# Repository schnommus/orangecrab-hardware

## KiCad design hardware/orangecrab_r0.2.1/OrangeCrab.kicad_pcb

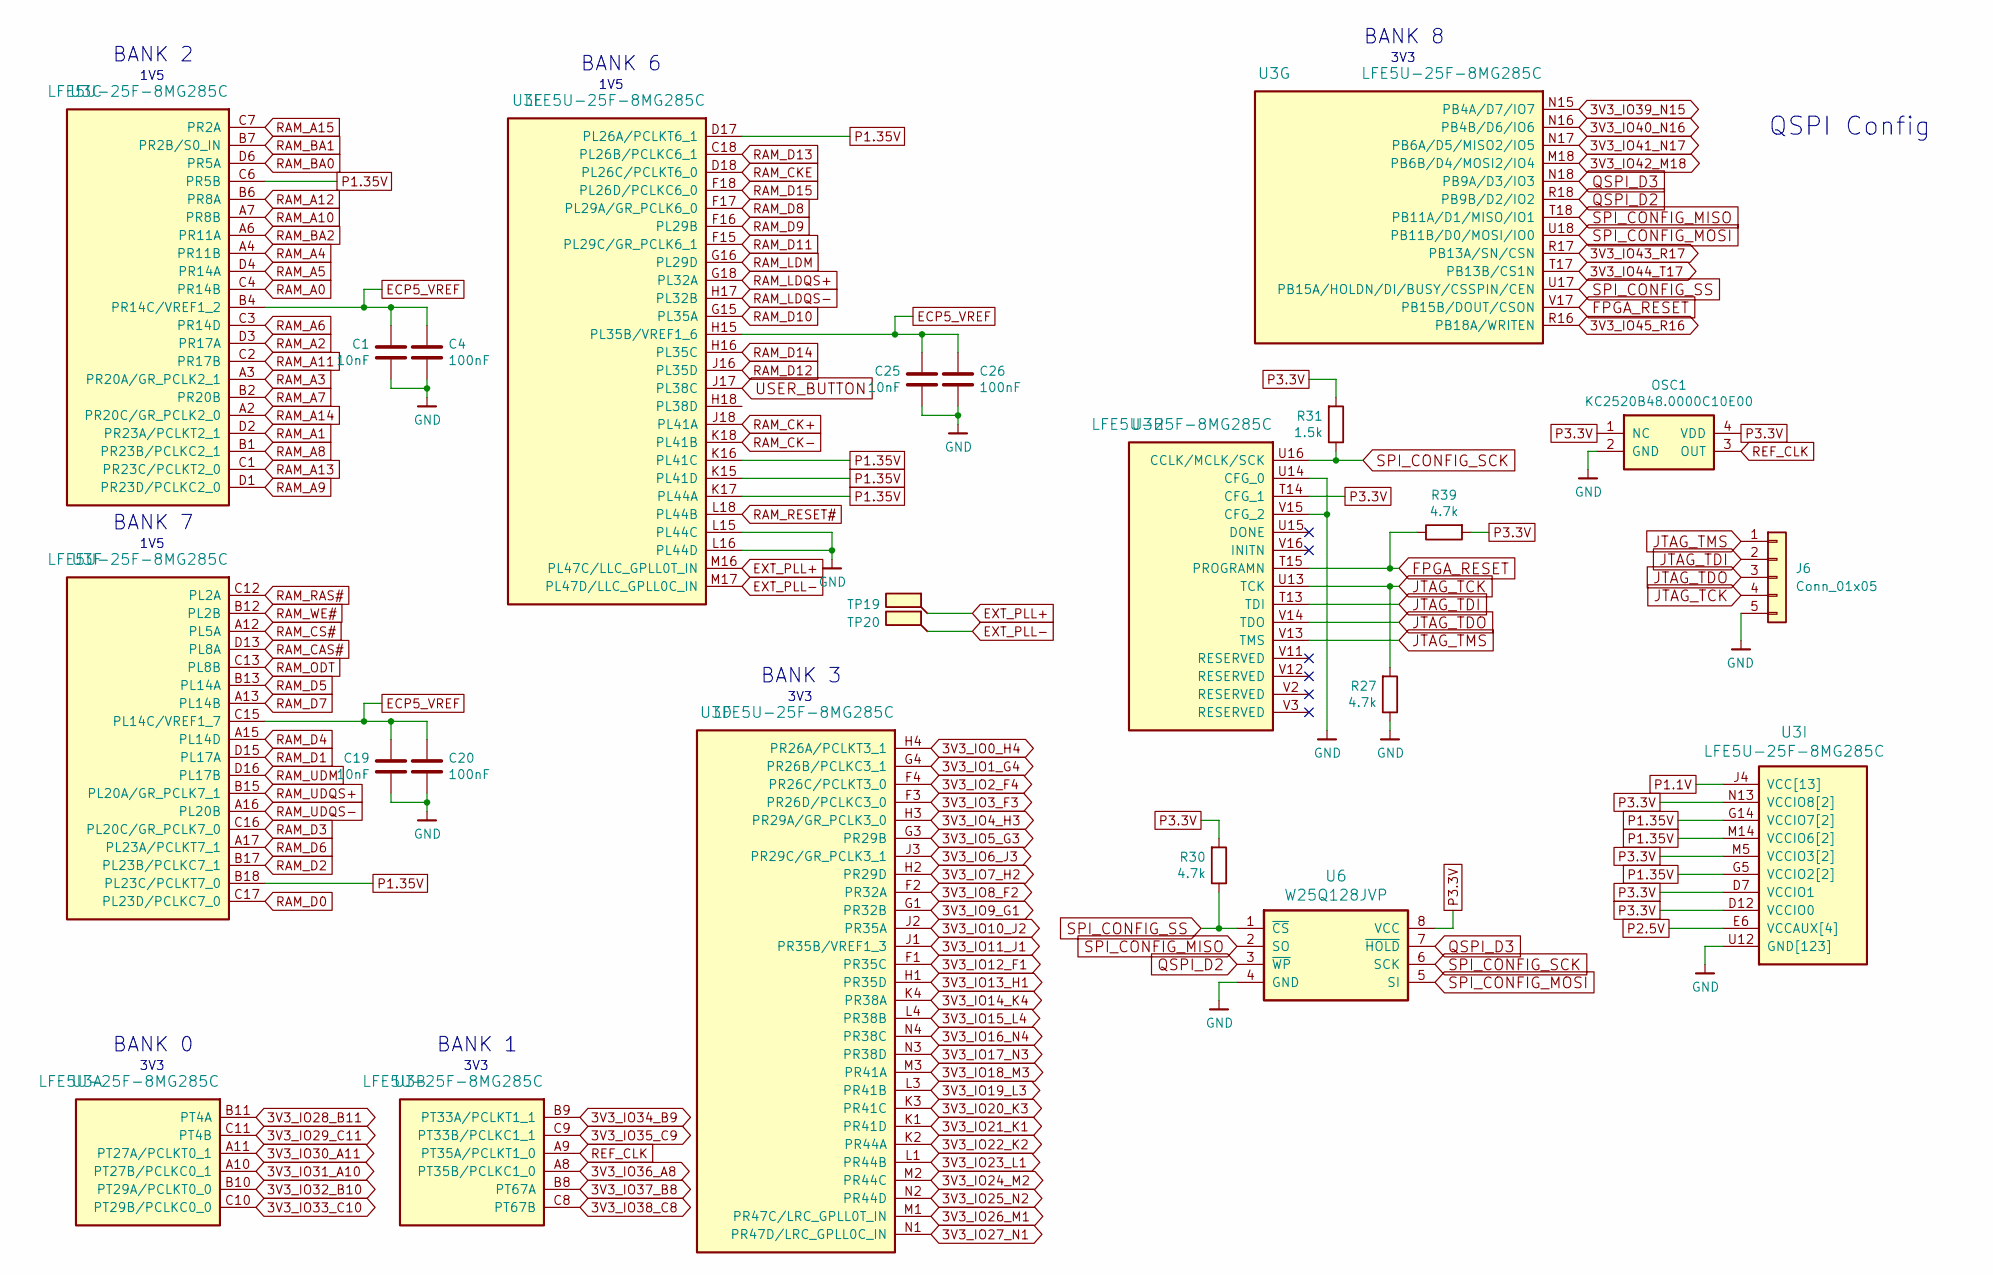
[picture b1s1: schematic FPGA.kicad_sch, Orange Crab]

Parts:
C1, C19, C25: 10nF; C_0201_0603Metric; lcsc# C272853
C4, C20, C26: 100nF; C_0201_0603Metric; lcsc# C467016
J6: Conn_01x05; PinHeader_1x05_P2.54mm_Vertical
OSC1: KC2520B48.0000C10E00; Oscilator_2.5x2.0; lcsc# C669070
R27, R30, R39: 4.7k; R_0201_0603Metric
R31: 1.5k; R_0201_0603Metric
TP19, TP20: SMD_TP; TestPoint_Pad_D0.5mm
U3: LFE5U-25F-8MG285C; csBGA285
U6: W25Q128JVP; WSON-8-1EP_6x5mm_P1.27mm_EP3.4x4mm; lcsc# C190862

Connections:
3V3_IO0_H4: U3.H4 (PR26A/PCLKT3_1); also elsewhere on the board
3V3_IO1_G4: U3.G4 (PR26B/PCLKC3_1); also elsewhere on the board
3V3_IO2_F4: U3.F4 (PR26C/PCLKT3_0); also elsewhere on the board
3V3_IO3_F3: U3.F3 (PR26D/PCLKC3_0); also elsewhere on the board
3V3_IO4_H3: U3.H3 (PR29A/GR_PCLK3_0); also elsewhere on the board
3V3_IO5_G3: U3.G3 (PR29B); also elsewhere on the board
3V3_IO6_J3: U3.J3 (PR29C/GR_PCLK3_1); also elsewhere on the board
3V3_IO7_H2: U3.H2 (PR29D); also elsewhere on the board
3V3_IO8_F2: U3.F2 (PR32A); also elsewhere on the board
3V3_IO9_G1: U3.G1 (PR32B); also elsewhere on the board
3V3_IO10_J2: U3.J2 (PR35A); also elsewhere on the board
3V3_IO11_J1: U3.J1 (PR35B/VREF1_3); also elsewhere on the board
3V3_IO12_F1: U3.F1 (PR35C); also elsewhere on the board
3V3_IO13_H1: U3.H1 (PR35D); also elsewhere on the board
3V3_IO14_K4: U3.K4 (PR38A); also elsewhere on the board
3V3_IO15_L4: U3.L4 (PR38B); also elsewhere on the board
3V3_IO16_N4: U3.N4 (PR38C); also elsewhere on the board
3V3_IO17_N3: U3.N3 (PR38D); also elsewhere on the board
3V3_IO18_M3: U3.M3 (PR41A); also elsewhere on the board
3V3_IO19_L3: U3.L3 (PR41B); also elsewhere on the board
3V3_IO20_K3: U3.K3 (PR41C); also elsewhere on the board
3V3_IO21_K1: U3.K1 (PR41D); also elsewhere on the board
3V3_IO22_K2: U3.K2 (PR44A); also elsewhere on the board
3V3_IO23_L1: U3.L1 (PR44B); also elsewhere on the board
3V3_IO24_M2: U3.M2 (PR44C); also elsewhere on the board
3V3_IO25_N2: U3.N2 (PR44D); also elsewhere on the board
3V3_IO26_M1: U3.M1 (PR47C/LRC_GPLL0T_IN); also elsewhere on the board
3V3_IO27_N1: U3.N1 (PR47D/LRC_GPLL0C_IN); also elsewhere on the board
3V3_IO28_B11: U3.B11 (PT4A); also elsewhere on the board
3V3_IO29_C11: U3.C11 (PT4B); also elsewhere on the board
3V3_IO30_A11: U3.A11 (PT27A/PCLKT0_1); also elsewhere on the board
3V3_IO31_A10: U3.A10 (PT27B/PCLKC0_1); also elsewhere on the board
3V3_IO32_B10: U3.B10 (PT29A/PCLKT0_0); also elsewhere on the board
3V3_IO33_C10: U3.C10 (PT29B/PCLKC0_0); also elsewhere on the board
3V3_IO34_B9: U3.B9 (PT33A/PCLKT1_1); also elsewhere on the board
3V3_IO35_C9: U3.C9 (PT33B/PCLKC1_1); also elsewhere on the board
3V3_IO36_A8: U3.A8 (PT35B/PCLKC1_0); also elsewhere on the board
3V3_IO37_B8: U3.B8 (PT67A); also elsewhere on the board
3V3_IO38_C8: U3.C8 (PT67B); also elsewhere on the board
3V3_IO39_N15: U3.N15 (PB4A/D7/IO7); also elsewhere on the board
3V3_IO40_N16: U3.N16 (PB4B/D6/IO6); also elsewhere on the board
3V3_IO41_N17: U3.N17 (PB6A/D5/MISO2/IO5); also elsewhere on the board
3V3_IO42_M18: U3.M18 (PB6B/D4/MOSI2/IO4); also elsewhere on the board
3V3_IO43_R17: U3.R17 (PB13A/SN/CSN); also elsewhere on the board
3V3_IO44_T17: U3.T17 (PB13B/CS1N); also elsewhere on the board
3V3_IO45_R16: U3.R16 (PB18A/WRITEN); also elsewhere on the board
ECP5_VREF: C1.1, C4.1, C19.1, C20.1, C25.1, C26.1, U3.B4 (PR14C/VREF1_2), U3.C15 (PL14C/VREF1_7), U3.H15 (PL35B/VREF1_6); also elsewhere on the board
EXT_PLL+: TP19.1, U3.M16 (PL47C/LLC_GPLL0T_IN)
EXT_PLL-: TP20.1, U3.M17 (PL47D/LLC_GPLL0C_IN)
FPGA_RESET: R39.1, U3.T15 (PROGRAMN), U3.V17 (PB15B/DOUT/CSON)
GND: C1.2, C4.2, C19.2, C20.2, C25.2, C26.2, J6.5, OSC1.2 (GND), R27.1, U3.B3 (GND[123]), U3.B16 (GND[123]), U3.E5 (GND[123]), U3.E7 (GND[123]), U3.E8 (GND[123]), U3.E9 (GND[123]), U3.E10 (GND[123]), U3.E11 (GND[123]), U3.E12 (GND[123]), U3.E14 (GND[123]), U3.F5 (GND[123]), U3.F6 (GND[123]), U3.F7 (GND[123]), U3.F8 (GND[123]), U3.F9 (GND[123]), U3.F10 (GND[123]), U3.F11 (GND[123]), U3.F12 (GND[123]), U3.F13 (GND[123]), U3.F14 (GND[123]), U3.G2 (GND[123]), U3.G6 (GND[123]), U3.G7 (GND[123]), U3.G8 (GND[123]), U3.G9 (GND[123]), U3.G10 (GND[123]), U3.G11 (GND[123]), U3.G12 (GND[123]), U3.G13 (GND[123]), U3.G17 (GND[123]), U3.H6 (GND[123]), U3.H7 (GND[123]), U3.H8 (GND[123]), U3.H9 (GND[123]), U3.H10 (GND[123]), U3.H11 (GND[123]), U3.H12 (GND[123]), U3.H13 (GND[123]), U3.J6 (GND[123]), U3.J7 (GND[123]), U3.J8 (GND[123]), U3.J9 (GND[123]), U3.J10 (GND[123]), U3.J11 (GND[123]), U3.J12 (GND[123]), U3.J13 (GND[123]), U3.K5 (GND[123]), U3.K6 (GND[123]), U3.K7 (GND[123]), U3.K8 (GND[123]), U3.K9 (GND[123]), U3.K10 (GND[123]), U3.K11 (GND[123]), U3.K12 (GND[123]), U3.K13 (GND[123]), U3.K14 (GND[123]), U3.L2 (GND[123]), U3.L5 (GND[123]), U3.L6 (GND[123]), U3.L7 (GND[123]), U3.L8 (GND[123]), U3.L9 (GND[123]), U3.L10 (GND[123]), U3.L11 (GND[123]), U3.L12 (GND[123]), U3.L13 (GND[123]), U3.L14 (GND[123]), U3.L15 (PL44C), U3.L16 (PL44D), U3.L17 (GND[123]), U3.M6 (GND[123]), U3.M7 (GND[123]), U3.M8 (GND[123]), U3.M9 (GND[123]), U3.M10 (GND[123]), U3.M11 (GND[123]), U3.M12 (GND[123]), U3.M13 (GND[123]), U3.N7 (GND[123]), U3.N8 (GND[123]), U3.N9 (GND[123]), U3.N10 (GND[123]), U3.N11 (GND[123]), U3.N12 (GND[123]), U3.P5 (GND[123]), U3.P6 (GND[123]), U3.P8 (GND[123]), U3.P10 (GND[123]), U3.P12 (GND[123]), U3.R1 (GND[123]), U3.R2 (GND[123]), U3.R3 (GND[123]), U3.R10 (GND[123]), U3.T1 (GND[123]), U3.T2 (GND[123]), U3.T3 (GND[123]), U3.T4 (GND[123]), U3.T5 (GND[123]), U3.T6 (GND[123]), U3.T7 (GND[123]), U3.T8 (GND[123]), U3.T9 (GND[123]), U3.T10 (GND[123]), U3.T11 (GND[123]), U3.T12 (GND[123]), U3.T16 (GND[123]), U3.U1 (GND[123]), U3.U2 (GND[123]), U3.U3 (GND[123]), U3.U4 (GND[123]), U3.U5 (GND[123]), U3.U6 (GND[123]), U3.U7 (GND[123]), U3.U8 (GND[123]), U3.U9 (GND[123]), U3.U10 (GND[123]), U3.U11 (GND[123]), U3.U12 (GND[123]), U3.U14 (CFG_0), U3.V4 (GND[123]), U3.V5 (GND[123]), U3.V6 (GND[123]), U3.V7 (GND[123]), U3.V8 (GND[123]), U3.V9 (GND[123]), U3.V10 (GND[123]), U3.V15 (CFG_2), U6.4 (GND); also elsewhere on the board
JTAG_TCK: J6.4, R27.2, U3.U13 (TCK); also elsewhere on the board
JTAG_TDI: J6.2, U3.T13 (TDI); also elsewhere on the board
JTAG_TDO: J6.3, U3.V14 (TDO); also elsewhere on the board
JTAG_TMS: J6.1, U3.V13 (TMS); also elsewhere on the board
P1.1V: U3.D8 (VCC[13]), U3.D9 (VCC[13]), U3.D10 (VCC[13]), U3.D11 (VCC[13]), U3.J4 (VCC[13]), U3.J5 (VCC[13]), U3.J14 (VCC[13]), U3.J15 (VCC[13]), U3.M4 (VCC[13]), U3.M15 (VCC[13]), U3.P7 (VCC[13]), U3.P9 (VCC[13]), U3.P11 (VCC[13]); also elsewhere on the board
P1.35V: U3.B18 (PL23C/PCLKT7_0), U3.C6 (PR5B), U3.D17 (PL26A/PCLKT6_1), U3.G5 (VCCIO2[2]), U3.G14 (VCCIO7[2]), U3.H5 (VCCIO2[2]), U3.H14 (VCCIO7[2]), U3.K15 (PL41D), U3.K16 (PL41C), U3.K17 (PL44A), U3.M14 (VCCIO6[2]), U3.N14 (VCCIO6[2]); also elsewhere on the board
P2.5V: U3.E6 (VCCAUX[4]), U3.E13 (VCCAUX[4]), U3.N6 (VCCAUX[4]), U3.P13 (VCCAUX[4]); also elsewhere on the board
P3.3V: OSC1.1 (NC), OSC1.4 (VDD), R30.2, R31.2, R39.2, U3.D7 (VCCIO1), U3.D12 (VCCIO0), U3.M5 (VCCIO3[2]), U3.N5 (VCCIO3[2]), U3.N13 (VCCIO8[2]), U3.P14 (VCCIO8[2]), U3.T14 (CFG_1), U6.8 (VCC); also elsewhere on the board
QSPI_D2: U3.R18 (PB9B/D2/IO2), U6.3 (~WP)
QSPI_D3: U3.N18 (PB9A/D3/IO3), U6.7 (~HOLD)
RAM_A0: U3.C4 (PR14B); also elsewhere on the board
RAM_A1: U3.D2 (PR23A/PCLKT2_1); also elsewhere on the board
RAM_A2: U3.D3 (PR17A); also elsewhere on the board
RAM_A3: U3.A3 (PR20A/GR_PCLK2_1); also elsewhere on the board
RAM_A4: U3.A4 (PR11B); also elsewhere on the board
RAM_A5: U3.D4 (PR14A); also elsewhere on the board
RAM_A6: U3.C3 (PR14D); also elsewhere on the board
RAM_A7: U3.B2 (PR20B); also elsewhere on the board
RAM_A8: U3.B1 (PR23B/PCLKC2_1); also elsewhere on the board
RAM_A9: U3.D1 (PR23D/PCLKC2_0); also elsewhere on the board
RAM_A10: U3.A7 (PR8B); also elsewhere on the board
RAM_A11: U3.C2 (PR17B); also elsewhere on the board
RAM_A12: U3.B6 (PR8A); also elsewhere on the board
RAM_A13: U3.C1 (PR23C/PCLKT2_0); also elsewhere on the board
RAM_A14: U3.A2 (PR20C/GR_PCLK2_0); also elsewhere on the board
RAM_A15: U3.C7 (PR2A); also elsewhere on the board
RAM_BA0: U3.D6 (PR5A); also elsewhere on the board
RAM_BA1: U3.B7 (PR2B/S0_IN); also elsewhere on the board
RAM_BA2: U3.A6 (PR11A); also elsewhere on the board
RAM_CAS#: U3.D13 (PL8A); also elsewhere on the board
RAM_CK+: U3.J18 (PL41A); also elsewhere on the board
RAM_CK-: U3.K18 (PL41B); also elsewhere on the board
RAM_CKE: U3.D18 (PL26C/PCLKT6_0); also elsewhere on the board
RAM_CS#: U3.A12 (PL5A); also elsewhere on the board
RAM_D0: U3.C17 (PL23D/PCLKC7_0); also elsewhere on the board
RAM_D1: U3.D15 (PL17A); also elsewhere on the board
RAM_D2: U3.B17 (PL23B/PCLKC7_1); also elsewhere on the board
RAM_D3: U3.C16 (PL20C/GR_PCLK7_0); also elsewhere on the board
RAM_D4: U3.A15 (PL14D); also elsewhere on the board
RAM_D5: U3.B13 (PL14A); also elsewhere on the board
RAM_D6: U3.A17 (PL23A/PCLKT7_1); also elsewhere on the board
RAM_D7: U3.A13 (PL14B); also elsewhere on the board
RAM_D8: U3.F17 (PL29A/GR_PCLK6_0); also elsewhere on the board
RAM_D9: U3.F16 (PL29B); also elsewhere on the board
RAM_D10: U3.G15 (PL35A); also elsewhere on the board
RAM_D11: U3.F15 (PL29C/GR_PCLK6_1); also elsewhere on the board
RAM_D12: U3.J16 (PL35D); also elsewhere on the board
RAM_D13: U3.C18 (PL26B/PCLKC6_1); also elsewhere on the board
RAM_D14: U3.H16 (PL35C); also elsewhere on the board
RAM_D15: U3.F18 (PL26D/PCLKC6_0); also elsewhere on the board
RAM_LDM: U3.G16 (PL29D); also elsewhere on the board
RAM_LDQS+: U3.G18 (PL32A); also elsewhere on the board
RAM_LDQS-: U3.H17 (PL32B); also elsewhere on the board
RAM_ODT: U3.C13 (PL8B); also elsewhere on the board
RAM_RAS#: U3.C12 (PL2A); also elsewhere on the board
RAM_RESET#: U3.L18 (PL44B); also elsewhere on the board
RAM_UDM: U3.D16 (PL17B); also elsewhere on the board
RAM_UDQS+: U3.B15 (PL20A/GR_PCLK7_1); also elsewhere on the board
RAM_UDQS-: U3.A16 (PL20B); also elsewhere on the board
RAM_WE#: U3.B12 (PL2B); also elsewhere on the board
REF_CLK: OSC1.3 (OUT), U3.A9 (PT35A/PCLKT1_0)
SPI_CONFIG_MISO: U3.T18 (PB11A/D1/MISO/IO1), U6.2 (SO)
SPI_CONFIG_MOSI: U3.U18 (PB11B/D0/MOSI/IO0), U6.5 (SI)
SPI_CONFIG_SCK: R31.1, U3.U16 (CCLK/MCLK/SCK), U6.6 (SCK)
SPI_CONFIG_SS: R30.1, U3.U17 (PB15A/HOLDN/DI/BUSY/CSSPIN/CEN), U6.1 (~CS)
USER_BUTTON: U3.J17 (PL38C)

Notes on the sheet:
BANK 0
3V3
BANK 8
1V5
BANK 6
BANK 1
3V3
1V5
QSPI Config
BANK 7
BANK 2
BANK 3

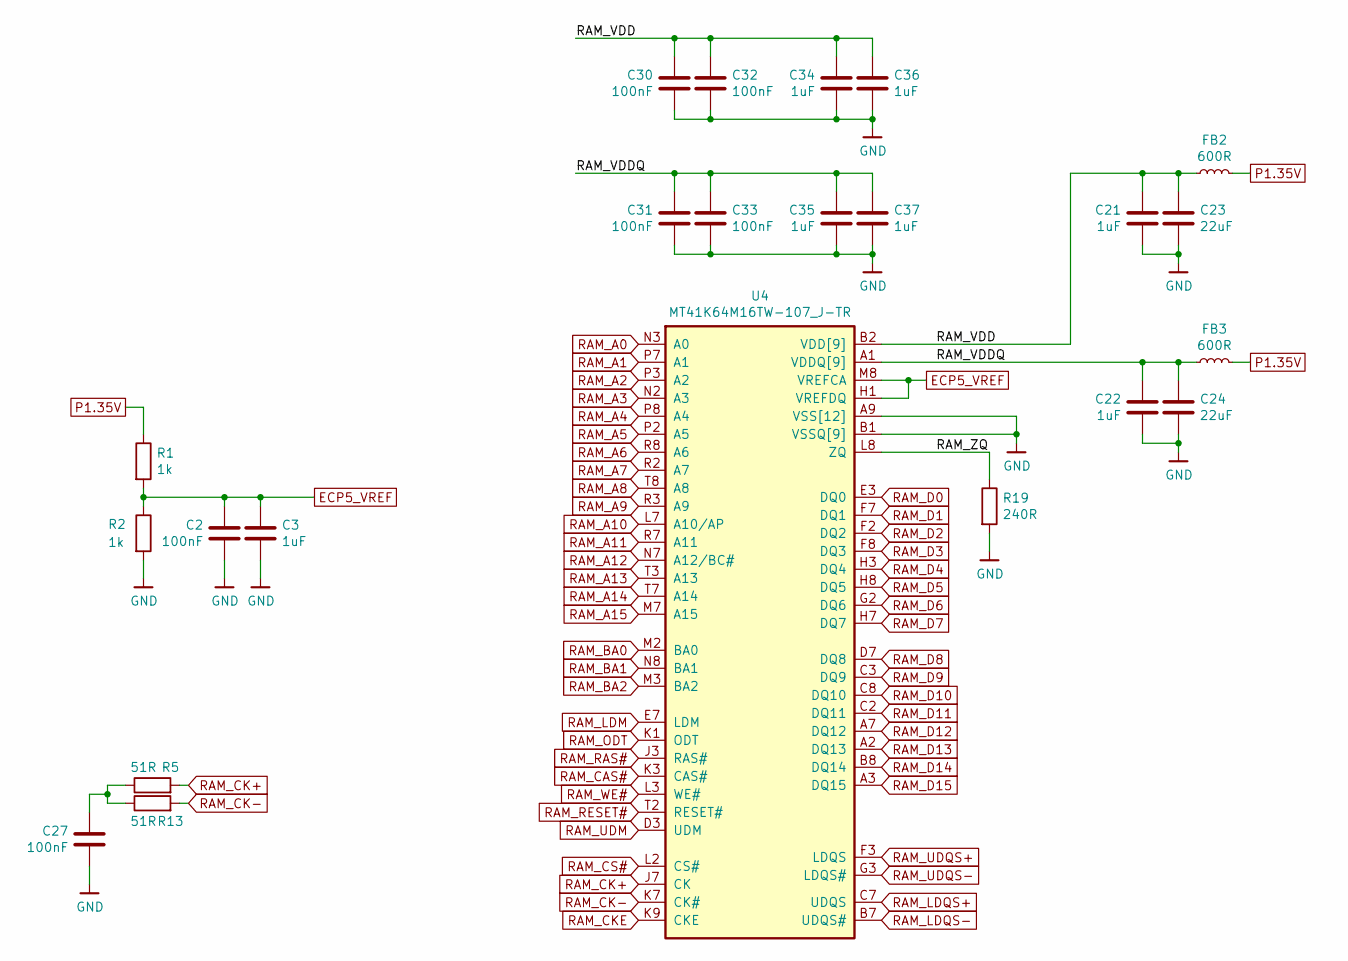
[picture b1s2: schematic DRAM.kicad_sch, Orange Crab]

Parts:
C2, C27, C30, C31, C32, C33: 100nF; C_0201_0603Metric; lcsc# C467016
C3, C21, C22, C34, C35, C36, C37: 1uF; C_0402_1005Metric; lcsc# C325464
C23, C24: 22uF; C_0603_1608Metric; lcsc# C109448
FB2, FB3: 600R; L_0402_1005Metric; lcsc# C87550
R1, R2: 1k; R_0201_0603Metric
R5, R13: 51R; R_0201_0603Metric
R19: 240R; R_0402_1005Metric
U4: MT41K64M16TW-107_J-TR; BGA-96_9.0x13.0mm_Layout2x3x16_P0.8mm; lcsc# C75475

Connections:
/DRAM/RAM_VDD: C21.1, C23.1, C30.1, C32.1, C34.1, C36.1, FB2.1, U4.B2 (VDD[9]), U4.D9 (VDD), U4.G7 (VDD), U4.K2 (VDD), U4.K8 (VDD), U4.N1 (VDD), U4.N9 (VDD), U4.R1 (VDD), U4.R9 (VDD)
/DRAM/RAM_VDDQ: C22.1, C24.1, C31.1, C33.1, C35.1, C37.1, FB3.1, U4.A1 (VDDQ[9]), U4.A8 (VDDQ), U4.C1 (VDDQ), U4.C9 (VDDQ), U4.D2 (VDDQ), U4.E9 (VDDQ), U4.F1 (VDDQ), U4.H2 (VDDQ), U4.H9 (VDDQ)
/DRAM/RAM_ZQ: R19.1, U4.L8 (ZQ)
ECP5_VREF: C2.1, C3.1, R1.2, R2.1, U4.H1 (VREFDQ), U4.M8 (VREFCA); also elsewhere on the board
GND: C2.2, C3.2, C21.2, C22.2, C23.2, C24.2, C27.2, C30.2, C31.2, C32.2, C33.2, C34.2, C35.2, C36.2, C37.2, R2.2, R19.2, U4.A9 (VSS[12]), U4.B1 (VSSQ[9]), U4.B3 (VSS), U4.B9 (VSSQ), U4.D1 (VSSQ), U4.D8 (VSSQ), U4.E1 (VSS), U4.E2 (VSSQ), U4.E8 (VSSQ), U4.F9 (VSSQ), U4.G1 (VSSQ), U4.G9 (VSSQ), U4.J2 (VSS), U4.J8 (VSS), U4.M1 (VSS), U4.M9 (VSS), U4.P1 (VSS), U4.P9 (VSS), U4.T1 (VSS), U4.T9 (VSS); also elsewhere on the board
unnamed: C27.1, R5.1, R13.1
P1.35V: FB2.2, FB3.2, R1.1; also elsewhere on the board
RAM_A0: U4.N3 (A0); also elsewhere on the board
RAM_A1: U4.P7 (A1); also elsewhere on the board
RAM_A2: U4.P3 (A2); also elsewhere on the board
RAM_A3: U4.N2 (A3); also elsewhere on the board
RAM_A4: U4.P8 (A4); also elsewhere on the board
RAM_A5: U4.P2 (A5); also elsewhere on the board
RAM_A6: U4.R8 (A6); also elsewhere on the board
RAM_A7: U4.R2 (A7); also elsewhere on the board
RAM_A8: U4.T8 (A8); also elsewhere on the board
RAM_A9: U4.R3 (A9); also elsewhere on the board
RAM_A10: U4.L7 (A10/AP); also elsewhere on the board
RAM_A11: U4.R7 (A11); also elsewhere on the board
RAM_A12: U4.N7 (A12/BC#); also elsewhere on the board
RAM_A13: U4.T3 (A13); also elsewhere on the board
RAM_A14: U4.T7 (A14); also elsewhere on the board
RAM_A15: U4.M7 (A15); also elsewhere on the board
RAM_BA0: U4.M2 (BA0); also elsewhere on the board
RAM_BA1: U4.N8 (BA1); also elsewhere on the board
RAM_BA2: U4.M3 (BA2); also elsewhere on the board
RAM_CAS#: U4.K3 (CAS#); also elsewhere on the board
RAM_CK+: R5.2, U4.J7 (CK); also elsewhere on the board
RAM_CK-: R13.2, U4.K7 (CK#); also elsewhere on the board
RAM_CKE: U4.K9 (CKE); also elsewhere on the board
RAM_CS#: U4.L2 (CS#); also elsewhere on the board
RAM_D0: U4.E3 (DQ0); also elsewhere on the board
RAM_D1: U4.F7 (DQ1); also elsewhere on the board
RAM_D2: U4.F2 (DQ2); also elsewhere on the board
RAM_D3: U4.F8 (DQ3); also elsewhere on the board
RAM_D4: U4.H3 (DQ4); also elsewhere on the board
RAM_D5: U4.H8 (DQ5); also elsewhere on the board
RAM_D6: U4.G2 (DQ6); also elsewhere on the board
RAM_D7: U4.H7 (DQ7); also elsewhere on the board
RAM_D8: U4.D7 (DQ8); also elsewhere on the board
RAM_D9: U4.C3 (DQ9); also elsewhere on the board
RAM_D10: U4.C8 (DQ10); also elsewhere on the board
RAM_D11: U4.C2 (DQ11); also elsewhere on the board
RAM_D12: U4.A7 (DQ12); also elsewhere on the board
RAM_D13: U4.A2 (DQ13); also elsewhere on the board
RAM_D14: U4.B8 (DQ14); also elsewhere on the board
RAM_D15: U4.A3 (DQ15); also elsewhere on the board
RAM_LDM: U4.E7 (LDM); also elsewhere on the board
RAM_LDQS+: U4.C7 (UDQS); also elsewhere on the board
RAM_LDQS-: U4.B7 (UDQS#); also elsewhere on the board
RAM_ODT: U4.K1 (ODT); also elsewhere on the board
RAM_RAS#: U4.J3 (RAS#); also elsewhere on the board
RAM_RESET#: U4.T2 (RESET#); also elsewhere on the board
RAM_UDM: U4.D3 (UDM); also elsewhere on the board
RAM_UDQS+: U4.F3 (LDQS); also elsewhere on the board
RAM_UDQS-: U4.G3 (LDQS#); also elsewhere on the board
RAM_WE#: U4.L3 (WE#); also elsewhere on the board

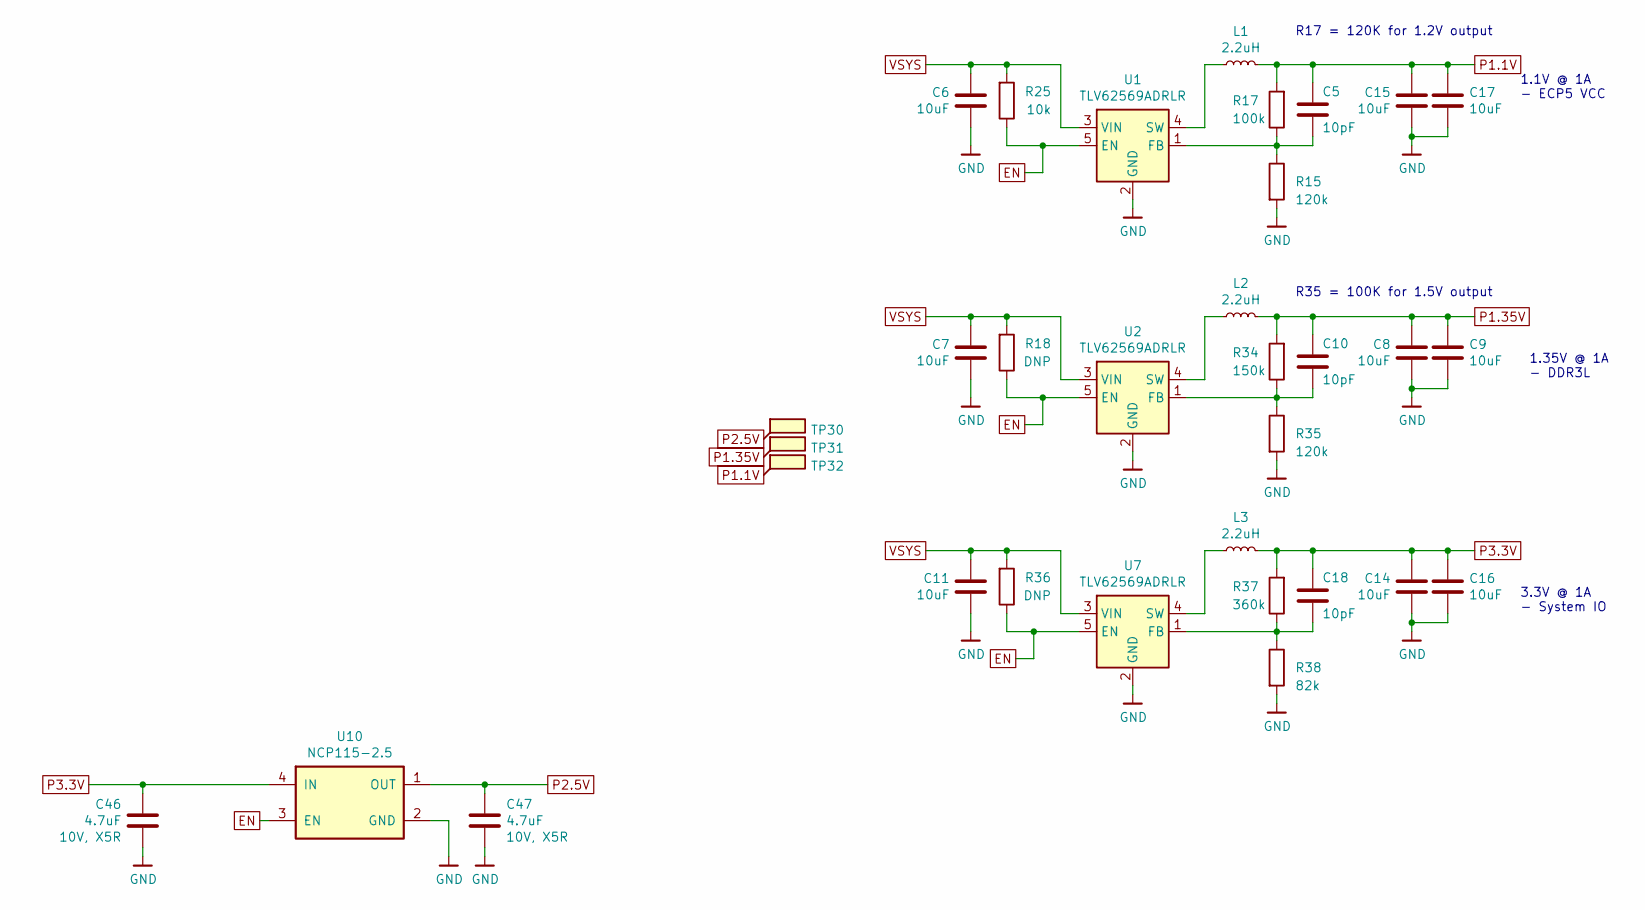
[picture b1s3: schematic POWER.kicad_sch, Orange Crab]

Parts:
C5, C10, C18: 10pF; C_0201_0603Metric; lcsc# C526922
C6, C7, C8, C9, C11, C14, C15, C16, C17: 10uF; C_0402_1005Metric; lcsc# C105884
C46, C47: 4.7uF; C_0402_1005Metric; lcsc# C326586
L1, L2, L3: 2.2uH; L_0805_2012Metric; lcsc# C216156
R15, R35: 120k; R_0201_0603Metric
R17: 100k; R_0201_0603Metric
R18, R36: DNP; R_0201_0603Metric
R25: 10k; R_0201_0603Metric
R34: 150k; R_0201_0603Metric
R37: 360k; R_0201_0603Metric
R38: 82k; R_0201_0603Metric
TP30, TP31, TP32: SMD_TP; TestPoint_Pad_D0.5mm
U1, U2, U7: TLV62569ADRLR; SOT-563; lcsc# C398367
U10: NCP115-2.5; Texas_X2SON-4_1x1mm_P0.65mm

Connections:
EN: R18.1, R25.1, R36.1, U1.5 (EN), U2.5 (EN), U7.5 (EN), U10.3 (EN)
GND: C6.1, C7.1, C8.1, C9.1, C11.1, C14.1, C15.1, C16.1, C17.1, C46.2, C47.2, R15.2, R35.2, R38.2, U1.2 (GND), U2.2 (GND), U7.2 (GND), U10.2 (GND); also elsewhere on the board
unnamed: C5.1, R15.1, R17.1, U1.1 (FB)
unnamed: L1.1, U1.4 (SW)
unnamed: C10.1, R34.1, R35.1, U2.1 (FB)
unnamed: L2.1, U2.4 (SW)
unnamed: C18.1, R37.1, R38.1, U7.1 (FB)
unnamed: L3.1, U7.4 (SW)
P1.1V: C5.2, C15.2, C17.2, L1.2, R17.2, TP32.1; also elsewhere on the board
P1.35V: C8.2, C9.2, C10.2, L2.2, R34.2, TP31.1; also elsewhere on the board
P2.5V: C47.1, TP30.1, U10.1 (OUT); also elsewhere on the board
P3.3V: C14.2, C16.2, C18.2, C46.1, L3.2, R37.2, U10.4 (IN); also elsewhere on the board
VSYS: C6.2, C7.2, C11.2, R18.2, R25.2, R36.2, U1.3 (VIN), U2.3 (VIN), U7.3 (VIN); also elsewhere on the board

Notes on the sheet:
1.35V @ 1A - DDR3L
3.3V @ 1A - System IO
R35 = 100K for 1.5V output
R17 = 120K for 1.2V output
1.1V @ 1A - ECP5 VCC

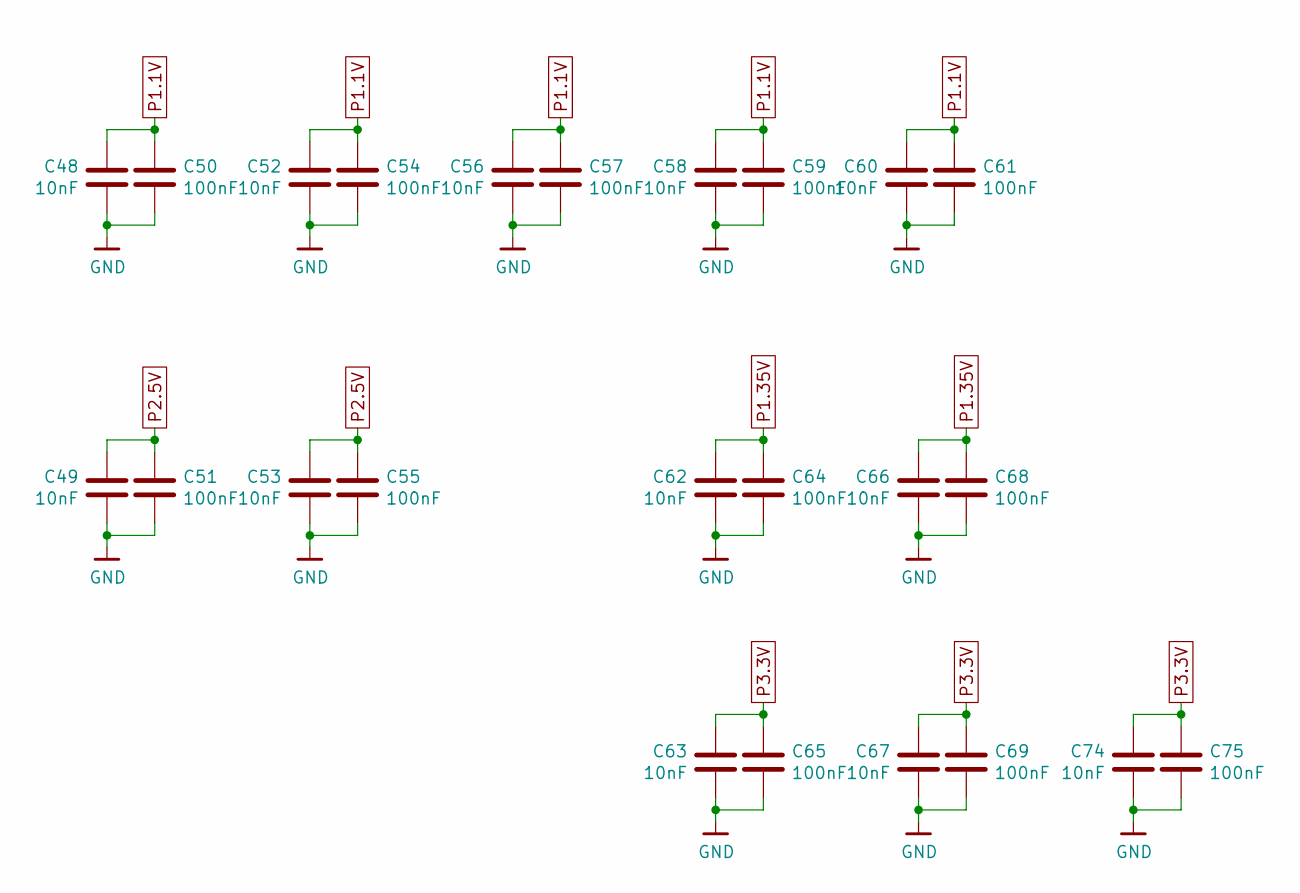
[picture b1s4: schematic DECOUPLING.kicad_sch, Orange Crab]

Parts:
C48, C49, C52, C53, C56, C58, C60, C62, C63, C66, C67, C74: 10nF; C_0201_0603Metric; lcsc# C272853
C50, C51, C54, C55, C57, C59, C61, C64, C65, C68, C69, C75: 100nF; C_0201_0603Metric; lcsc# C467016

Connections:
GND: C48.2, C49.2, C50.2, C51.2, C52.2, C53.2, C54.2, C55.2, C56.2, C57.2, C58.2, C59.2, C60.2, C61.2, C62.2, C63.2, C64.2, C65.2, C66.2, C67.2, C68.2, C69.2, C74.2, C75.2; also elsewhere on the board
P1.1V: C48.1, C50.1, C52.1, C54.1, C56.1, C57.1, C58.1, C59.1, C60.1, C61.1; also elsewhere on the board
P1.35V: C62.1, C64.1, C66.1, C68.1; also elsewhere on the board
P2.5V: C49.1, C51.1, C53.1, C55.1; also elsewhere on the board
P3.3V: C63.1, C65.1, C67.1, C69.1, C74.1, C75.1; also elsewhere on the board

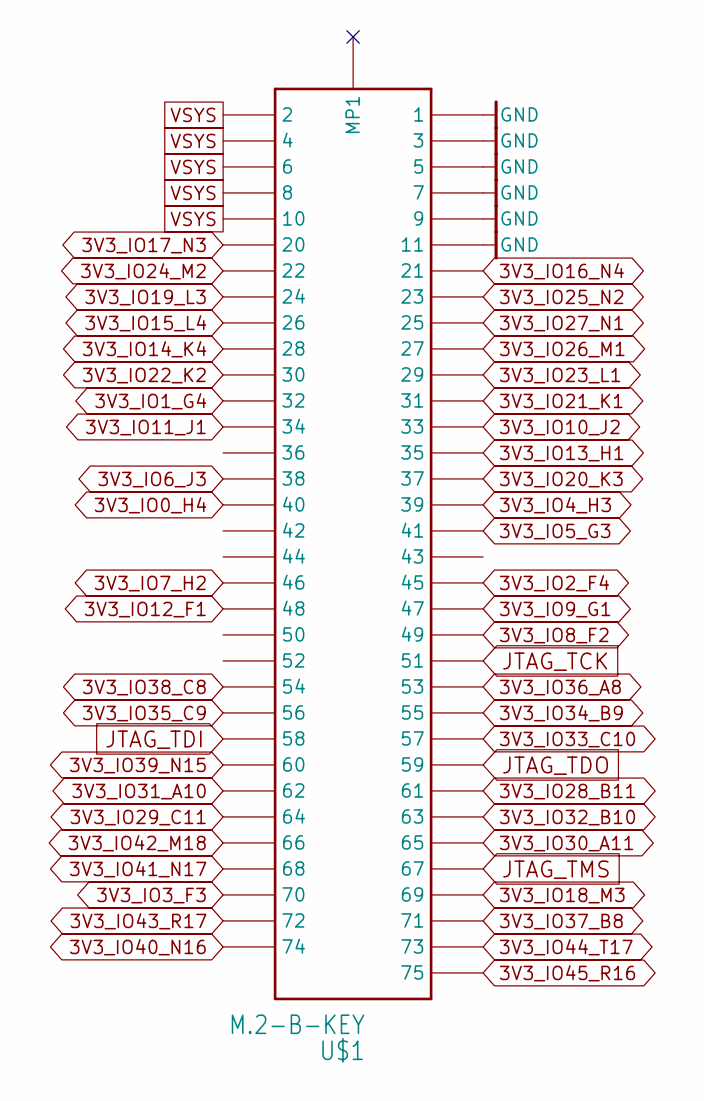
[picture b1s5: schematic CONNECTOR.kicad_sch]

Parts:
U$1: M.2-B-KEY

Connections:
3V3_IO0_H4: U$1.P$40 (40); also elsewhere on the board
3V3_IO1_G4: U$1.P$32 (32); also elsewhere on the board
3V3_IO2_F4: U$1.P$45 (45); also elsewhere on the board
3V3_IO3_F3: U$1.P$70 (70); also elsewhere on the board
3V3_IO4_H3: U$1.P$39 (39); also elsewhere on the board
3V3_IO5_G3: U$1.P$41 (41); also elsewhere on the board
3V3_IO6_J3: U$1.P$38 (38); also elsewhere on the board
3V3_IO7_H2: U$1.P$46 (46); also elsewhere on the board
3V3_IO8_F2: U$1.P$49 (49); also elsewhere on the board
3V3_IO9_G1: U$1.P$47 (47); also elsewhere on the board
3V3_IO10_J2: U$1.P$33 (33); also elsewhere on the board
3V3_IO11_J1: U$1.P$34 (34); also elsewhere on the board
3V3_IO12_F1: U$1.P$48 (48); also elsewhere on the board
3V3_IO13_H1: U$1.P$35 (35); also elsewhere on the board
3V3_IO14_K4: U$1.P$28 (28); also elsewhere on the board
3V3_IO15_L4: U$1.P$26 (26); also elsewhere on the board
3V3_IO16_N4: U$1.P$21 (21); also elsewhere on the board
3V3_IO17_N3: U$1.P$20 (20); also elsewhere on the board
3V3_IO18_M3: U$1.P$69 (69); also elsewhere on the board
3V3_IO19_L3: U$1.P$24 (24); also elsewhere on the board
3V3_IO20_K3: U$1.P$37 (37); also elsewhere on the board
3V3_IO21_K1: U$1.P$31 (31); also elsewhere on the board
3V3_IO22_K2: U$1.P$30 (30); also elsewhere on the board
3V3_IO23_L1: U$1.P$29 (29); also elsewhere on the board
3V3_IO24_M2: U$1.P$22 (22); also elsewhere on the board
3V3_IO25_N2: U$1.P$23 (23); also elsewhere on the board
3V3_IO26_M1: U$1.P$27 (27); also elsewhere on the board
3V3_IO27_N1: U$1.P$25 (25); also elsewhere on the board
3V3_IO28_B11: U$1.P$61 (61); also elsewhere on the board
3V3_IO29_C11: U$1.P$64 (64); also elsewhere on the board
3V3_IO30_A11: U$1.P$65 (65); also elsewhere on the board
3V3_IO31_A10: U$1.P$62 (62); also elsewhere on the board
3V3_IO32_B10: U$1.P$63 (63); also elsewhere on the board
3V3_IO33_C10: U$1.P$57 (57); also elsewhere on the board
3V3_IO34_B9: U$1.P$55 (55); also elsewhere on the board
3V3_IO35_C9: U$1.P$56 (56); also elsewhere on the board
3V3_IO36_A8: U$1.P$53 (53); also elsewhere on the board
3V3_IO37_B8: U$1.P$71 (71); also elsewhere on the board
3V3_IO38_C8: U$1.P$54 (54); also elsewhere on the board
3V3_IO39_N15: U$1.P$60 (60); also elsewhere on the board
3V3_IO40_N16: U$1.P$74 (74); also elsewhere on the board
3V3_IO41_N17: U$1.P$68 (68); also elsewhere on the board
3V3_IO42_M18: U$1.P$66 (66); also elsewhere on the board
3V3_IO43_R17: U$1.P$72 (72); also elsewhere on the board
3V3_IO44_T17: U$1.P$73 (73); also elsewhere on the board
3V3_IO45_R16: U$1.P$75 (75); also elsewhere on the board
GND: U$1.P$1 (1), U$1.P$3 (3), U$1.P$5 (5), U$1.P$7 (7), U$1.P$9 (9), U$1.P$11 (11); also elsewhere on the board
JTAG_TCK: U$1.P$51 (51); also elsewhere on the board
JTAG_TDI: U$1.P$58 (58); also elsewhere on the board
JTAG_TDO: U$1.P$59 (59); also elsewhere on the board
JTAG_TMS: U$1.P$67 (67); also elsewhere on the board
VSYS: U$1.P$2 (2), U$1.P$4 (4), U$1.P$6 (6), U$1.P$8 (8), U$1.P$10 (10); also elsewhere on the board

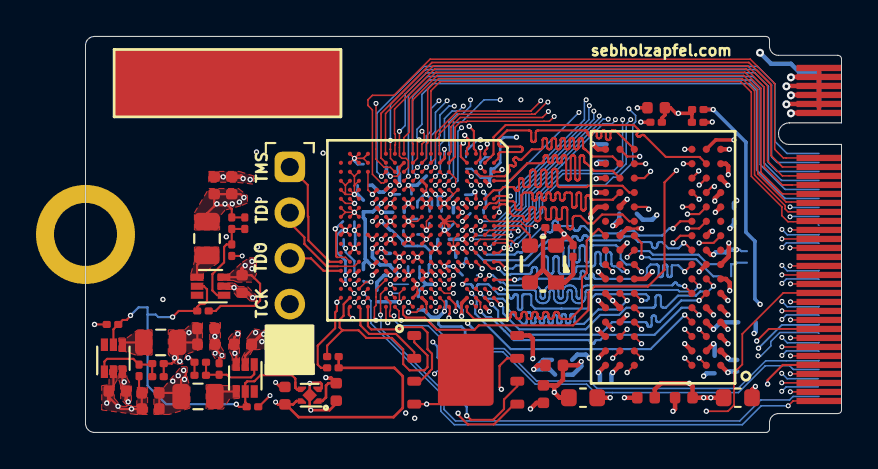
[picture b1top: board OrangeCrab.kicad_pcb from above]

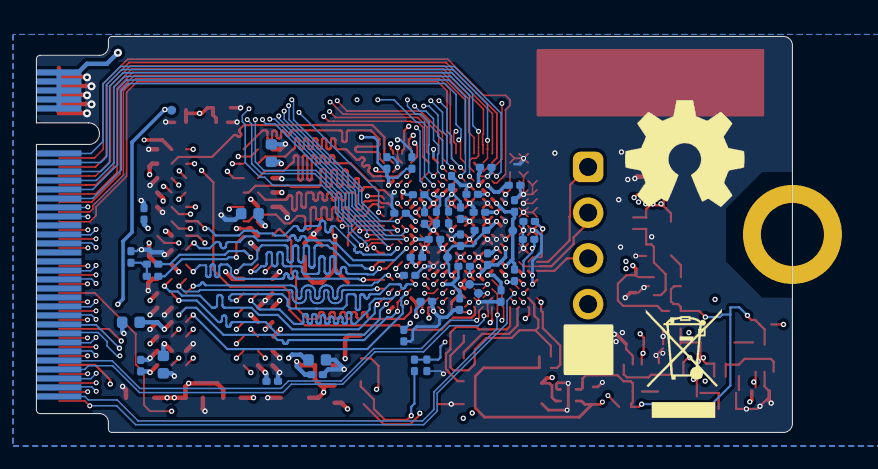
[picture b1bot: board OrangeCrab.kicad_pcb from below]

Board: 6 copper layers, 42.0 x 22.0 mm, 97 parts (47 on the bottom side), 128 nets.

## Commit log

2023-10-27 fix symbol links // try pcb/sch align
2023-10-27 all IO gone/cleaned
2023-10-27 more gnd/via cleanup
2023-10-28 M.2 form factor
2023-10-28 connect all spare IOs to M.2
2023-10-28 Clean up DRC a bit
2023-10-28 copy out fab notes
2023-10-28 dogbone out all FPGA IOs
2023-10-28 almost finished route bank0 without pinswap
2023-10-28 route done except final pinswap
2023-10-28 execute pinswap, not routed yet
2023-10-28 complete route, clear all DRC violations
2023-10-28 Clean up traces and silk
2023-10-29 add some LCSC part numbers, stock all important parts
2023-11-08 route JTAG to M.2 pads
2023-11-08 populate LCSC# for missing passives

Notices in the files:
hardware/orangecrab_r0.2.1/DECOUPLING.kicad_sch:
Licensed under CERN OHL v.1.2
